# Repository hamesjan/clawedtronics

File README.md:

Claw go down
Claw go up
You get Prize

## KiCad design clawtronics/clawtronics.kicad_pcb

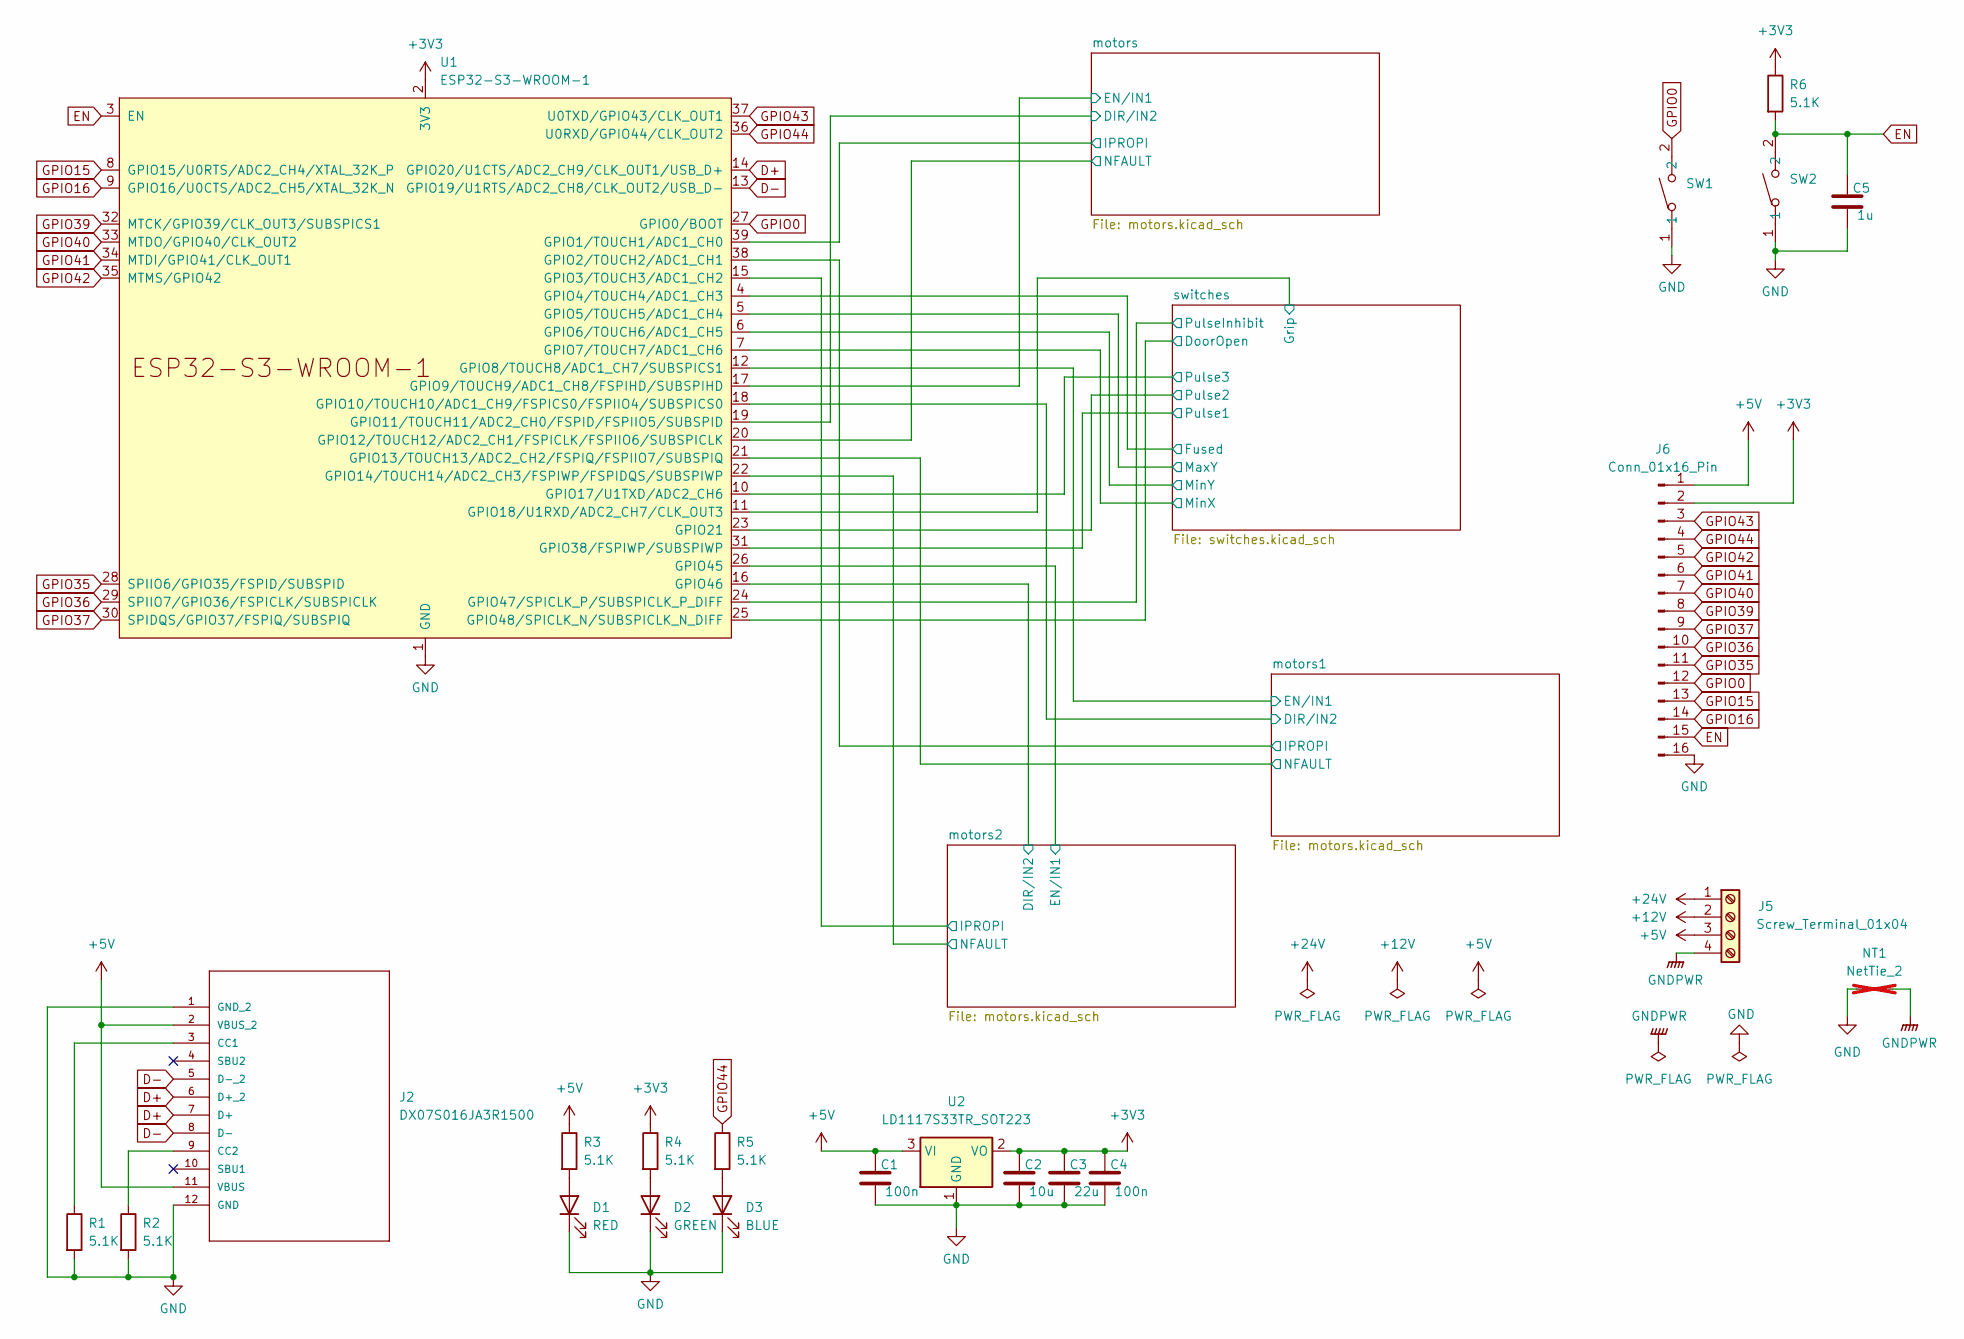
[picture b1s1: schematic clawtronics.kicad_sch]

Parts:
C1, C4: 100n; C_0603_1608Metric; Part Number C0603C104J3RACTU
C2: 10u; C_0603_1608Metric; Part Number 0603W106M6R3XD
C3: 22u; C_0603_1608Metric; Part Number 0603W226M100BD
C5: 1u; C_0603_1608Metric; Part Number 0603B105K100XD
D1: RED; LED_0603_1608Metric; Part Number SML-D12U8WT86
D2: GREEN; LED_0603_1608Metric; Part Number SML-D13M8WT86
D3: BLUE; LED_0603_1608Metric; Part Number SMLEN3BC8TT86
J2: DX07S016JA3R1500; CONN12_DX07S_JAE; MANUFACTURER_PART_NUMBER DX07S016JA3R1500
J5: Screw_Terminal_01x04; TerminalBlock_Phoenix_MKDS-1,5-4_1x04_P5.00mm_Horizontal; Part Number 1869088
J6: Conn_01x16_Pin; PinHeader_1x16_P1.00mm_Vertical; Part Number SM16B-SHLS-TF(LF)(SN)
NT1: NetTie_2; not fitted
R1, R2, R3, R4, R5, R6: 5.1K; R_0603_1608Metric; Part Number RC0603FR-105K1L
SW1, SW2: SW_SPST_TS-1088-xR020; Part Number GPTS203211B
U1: ESP32-S3-WROOM-1; Part Number ESP32-S3-WROOM-1U-N8R8
U2: LD1117S33TR_SOT223; SOT-223-3_TabPin2; Part Number LD1117S33TR

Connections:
+3V3: C2.1, C3.1, C4.1, J6.2, R4.1, R6.1, U1.2 (3V3), U2.2 (VO); also elsewhere on the board
+5V: C1.1, J2.2 (VBUS_2), J2.11 (VBUS), J5.3, J6.1, R3.1, U2.3 (VI); also elsewhere on the board
+12V: J5.2; also elsewhere on the board
+24V: J5.1; also elsewhere on the board
/motors1/DIR/IN2: U1.18 (GPIO10/TOUCH10/ADC1_CH9/FSPICS0/FSPIIO4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); also elsewhere on the board
/motors1/EN/IN1: U1.12 (GPIO8/TOUCH8/ADC1_CH7/SUBSPICS1); also elsewhere on the board
/motors1/IPROPI: U1.38 (GPIO2/TOUCH2/ADC1_CH1); also elsewhere on the board
/motors1/NFAULT: U1.21 (GPIO13/TOUCH13/ADC2_CH2/FSPIQ/FSPIIO7/S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); also elsewhere on the board
/motors2/DIR/IN2: U1.16 (GPIO46); also elsewhere on the board
/motors2/EN/IN1: U1.26 (GPIO45); also elsewhere on the board
/motors2/IPROPI: U1.15 (GPIO3/TOUCH3/ADC1_CH2); also elsewhere on the board
/motors2/NFAULT: U1.22 (GPIO14/TOUCH14/ADC2_CH3/FSPIWP/FSPIDQS/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); also elsewhere on the board
/motors/DIR/IN2: U1.19 (GPIO11/TOUCH11/ADC2_CH0/FSPID/FSPIIO5/S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); also elsewhere on the board
/motors/EN/IN1: U1.17 (GPIO9/TOUCH9/ADC1_CH8/FSPIHD/SUBSPIHD); also elsewhere on the board
/motors/IPROPI: U1.39 (GPIO1/TOUCH1/ADC1_CH0); also elsewhere on the board
/motors/NFAULT: U1.20 (GPIO12/TOUCH12/ADC2_CH1/FSPICLK/FSPIIO6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); also elsewhere on the board
/switches/DoorOpen: U1.25 (GPIO48/SPICLK_N/SUBSPICLK_N_DIFF); also elsewhere on the board
/switches/Fused: U1.4 (GPIO4/TOUCH4/ADC1_CH3); also elsewhere on the board
/switches/Grip: U1.11 (GPIO18/U1RXD/ADC2_CH7/CLK_OUT3); also elsewhere on the board
/switches/MaxY: U1.5 (GPIO5/TOUCH5/ADC1_CH4); also elsewhere on the board
/switches/MinX: U1.7 (GPIO7/TOUCH7/ADC1_CH6); also elsewhere on the board
/switches/MinY: U1.6 (GPIO6/TOUCH6/ADC1_CH5); also elsewhere on the board
/switches/Pulse1: U1.31 (GPIO38/FSPIWP/SUBSPIWP); also elsewhere on the board
/switches/Pulse2: U1.23 (GPIO21); also elsewhere on the board
/switches/Pulse3: U1.10 (GPIO17/U1TXD/ADC2_CH6); also elsewhere on the board
/switches/PulseInhibit: U1.24 (GPIO47/SPICLK_P/SUBSPICLK_P_DIFF); also elsewhere on the board
D+: J2.6 (D+_2), J2.7 (D+), U1.14 (GPIO20/U1CTS/ADC2_CH9/CLK_OUT1/USB_D+)
D-: J2.5 (D-_2), J2.8 (D-), U1.13 (GPIO19/U1RTS/ADC2_CH8/CLK_OUT2/USB_D-)
EN: C5.1, J6.15, R6.2, SW2.2, U1.3 (EN)
GND: C1.2, C2.2, C3.2, C4.2, C5.2, D1.1 (K), D2.1 (K), D3.1 (K), J2.1 (GND_2), J2.12 (GND), J6.16, NT1.1, R1.2, R2.2, SW1.1, SW2.1, U1.1 (GND), U1.40 (GND), U1.41 (GND), U2.1 (GND); also elsewhere on the board
GNDPWR: J5.4, NT1.2; also elsewhere on the board
GPIO0: J6.12, SW1.2, U1.27 (GPIO0/BOOT)
GPIO15: J6.13, U1.8 (GPIO15/U0RTS/ADC2_CH4/XTAL_32K_P)
GPIO16: J6.14, U1.9 (GPIO16/U0CTS/ADC2_CH5/XTAL_32K_N)
GPIO35: J6.11, U1.28 (SPIIO6/GPIO35/FSPID/SUBSPID)
GPIO36: J6.10, U1.29 (SPIIO7/GPIO36/FSPICLK/SUBSPICLK)
GPIO37: J6.9, U1.30 (SPIDQS/GPIO37/FSPIQ/SUBSPIQ)
GPIO39: J6.8, U1.32 (MTCK/GPIO39/CLK_OUT3/SUBSPICS1)
GPIO40: J6.7, U1.33 (MTDO/GPIO40/CLK_OUT2)
GPIO41: J6.6, U1.34 (MTDI/GPIO41/CLK_OUT1)
GPIO42: J6.5, U1.35 (MTMS/GPIO42)
GPIO43: J6.3, U1.37 (U0TXD/GPIO43/CLK_OUT1)
GPIO44: J6.4, R5.1, U1.36 (U0RXD/GPIO44/CLK_OUT2)
unnamed: D1.2 (A), R3.2
unnamed: D2.2 (A), R4.2
unnamed: D3.2 (A), R5.2
unnamed: J2.3 (CC1), R1.1
unnamed: J2.9 (CC2), R2.1

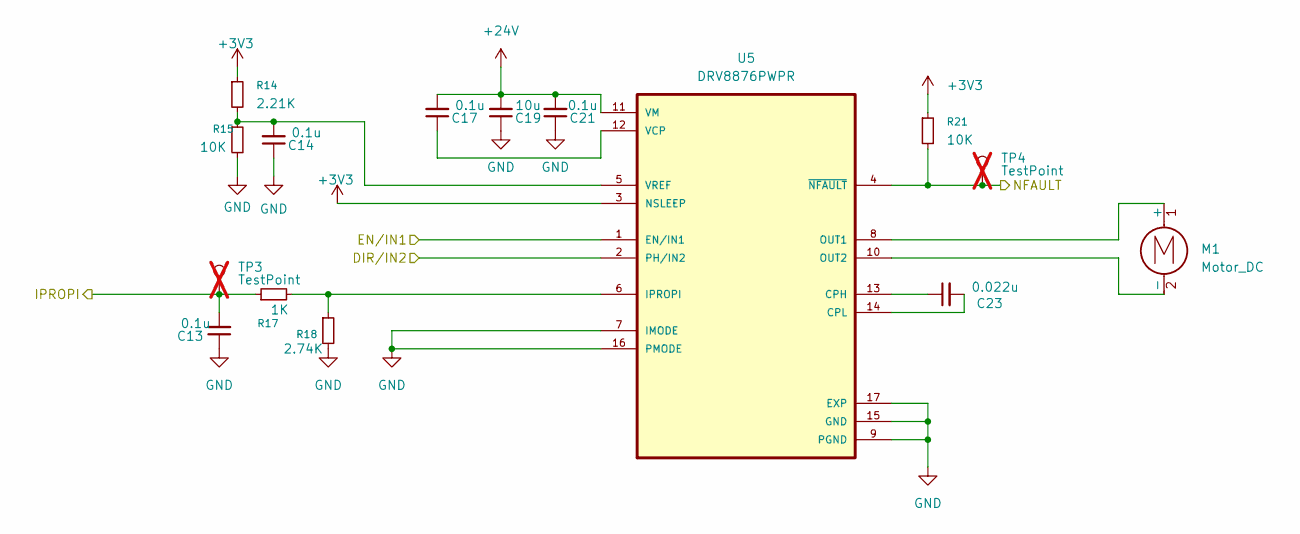
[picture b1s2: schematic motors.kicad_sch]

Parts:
C13, C14, C17, C21: 0.1u; C_0603_1608Metric; Part Number 0603B104K101XD
C19: 10u; C_0603_1608Metric; Part Number 0603W106M6R3XD
C23: 0.022u; C_0603_1608Metric; Part Number 0603B223K500SD
M1: Motor_DC; TerminalBlock_Phoenix_MKDS-1,5-2_1x02_P5.00mm_Horizontal; Part Number 1729128
R14: 2.21K; R_0603_1608Metric; Part Number RMCF0603FT2K21
R15, R21: 10K; R_0603_1608Metric; Part Number RC0603FR-0710KL
R17: 1K; R_0603_1608Metric; Part Number RMCF0603FT1K00
R18: 2.74K; R_0603_1608Metric; Part Number RMCF0603FT2K74
TP3, TP4: TestPoint; TestPoint_Pad_1.0x1.0mm; not fitted
U5: DRV8876PWPR; moto; PARTREV E

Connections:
+3V3: R14.1, R21.1, U5.3 (NSLEEP); also elsewhere on the board
+24V: C17.2, C19.2, C21.2, U5.11 (VM); also elsewhere on the board
/motors/DIR/IN2: U5.2 (PH/IN2); also elsewhere on the board
/motors/EN/IN1: U5.1 (EN/IN1); also elsewhere on the board
/motors/IPROPI: C13.2, R17.1, TP3.1 (1_1); also elsewhere on the board
/motors/NFAULT: R21.2, TP4.1 (1_1), U5.4 (~NFAULT); also elsewhere on the board
GND: C13.1, C14.1, C19.1, C21.1, R15.2, R18.2, U5.7 (IMODE), U5.9 (PGND), U5.15 (GND), U5.16 (PMODE), U5.17 (EXP); also elsewhere on the board
unnamed: M1.1 (+), U5.8 (OUT1)
unnamed: M1.2 (-), U5.10 (OUT2)
unnamed: C23.1, U5.13 (CPH)
unnamed: C23.2, U5.14 (CPL)
unnamed: R17.2, R18.1, U5.6 (IPROPI)
unnamed: C17.1, U5.12 (VCP)
unnamed: C14.2, R14.2, R15.1, U5.5 (VREF)

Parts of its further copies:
C15, C16, C18, C22, C25, C26, C27, C29: 0.1u; C_0603_1608Metric; Part Number 0603B104K101XD
C20, C28: 10u; C_0603_1608Metric; Part Number 0603W106M6R3XD
C24, C30: 0.022u; C_0603_1608Metric; Part Number 0603B223K500SD
M2, M3: Motor_DC; TerminalBlock_Phoenix_MKDS-1,5-2_1x02_P5.00mm_Horizontal; Part Number 1729128
R16, R24: 2.21K; R_0603_1608Metric; Part Number RMCF0603FT2K21
R19, R23, R25, R30: 10K; R_0603_1608Metric; Part Number RC0603FR-0710KL
R20, R26: 1K; R_0603_1608Metric; Part Number RMCF0603FT1K00
R22, R27: 2.74K; R_0603_1608Metric; Part Number RMCF0603FT2K74
TP5, TP6, TP7, TP9: TestPoint; TestPoint_Pad_1.0x1.0mm; not fitted
U7, U8: DRV8876PWPR; moto; PARTREV E

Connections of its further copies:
+3V3: R16.1, R23.1, R24.1, R30.1, U7.3 (NSLEEP), U8.3 (NSLEEP); also elsewhere on the board
+24V: C18.2, C20.2, C22.2, C27.2, C28.2, C29.2, U7.11 (VM), U8.11 (VM); also elsewhere on the board
/motors1/DIR/IN2: U7.2 (PH/IN2); also elsewhere on the board
/motors1/EN/IN1: U7.1 (EN/IN1); also elsewhere on the board
/motors1/IPROPI: C15.2, R20.1, TP5.1 (1_1); also elsewhere on the board
/motors1/NFAULT: R23.2, TP6.1 (1_1), U7.4 (~NFAULT); also elsewhere on the board
/motors2/DIR/IN2: U8.2 (PH/IN2); also elsewhere on the board
/motors2/EN/IN1: U8.1 (EN/IN1); also elsewhere on the board
/motors2/IPROPI: C25.2, R26.1, TP7.1 (1_1); also elsewhere on the board
/motors2/NFAULT: R30.2, TP9.1 (1_1), U8.4 (~NFAULT); also elsewhere on the board
GND: C15.1, C16.1, C20.1, C22.1, C25.1, C26.1, C28.1, C29.1, R19.2, R22.2, R25.2, R27.2, U7.7 (IMODE), U7.9 (PGND), U7.15 (GND), U7.16 (PMODE), U7.17 (EXP), U8.7 (IMODE), U8.9 (PGND), U8.15 (GND), U8.16 (PMODE), U8.17 (EXP); also elsewhere on the board
unnamed: M2.1 (+), U7.8 (OUT1)
unnamed: M2.2 (-), U7.10 (OUT2)
unnamed: M3.1 (+), U8.8 (OUT1)
unnamed: M3.2 (-), U8.10 (OUT2)
unnamed: C24.1, U7.13 (CPH)
unnamed: C24.2, U7.14 (CPL)
unnamed: R20.2, R22.1, U7.6 (IPROPI)
unnamed: C18.1, U7.12 (VCP)
unnamed: C16.2, R16.2, R19.1, U7.5 (VREF)
unnamed: C30.1, U8.13 (CPH)
unnamed: C30.2, U8.14 (CPL)
unnamed: R26.2, R27.1, U8.6 (IPROPI)
unnamed: C27.1, U8.12 (VCP)
unnamed: C26.2, R24.2, R25.1, U8.5 (VREF)

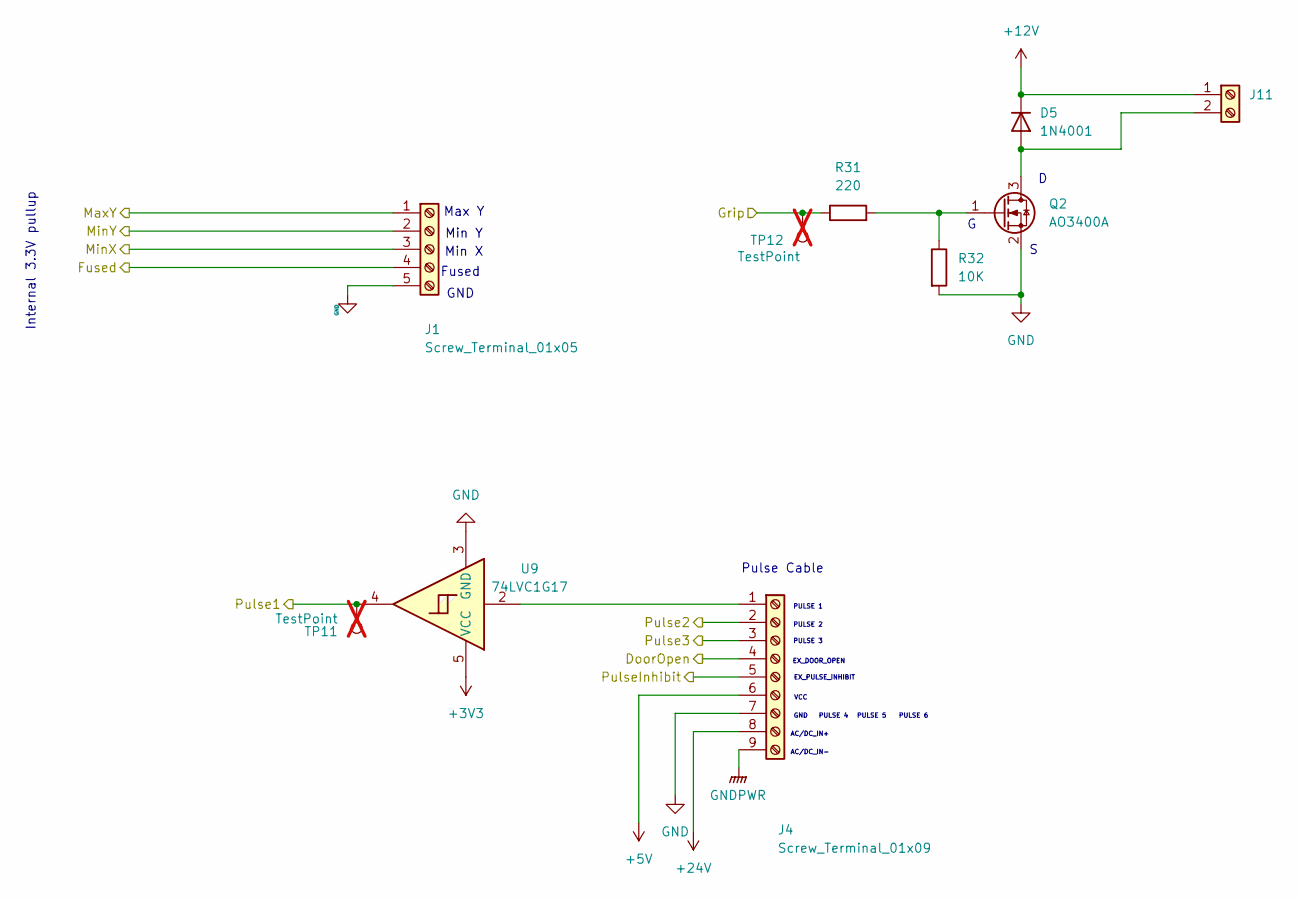
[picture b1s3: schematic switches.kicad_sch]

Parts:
D5: 1N4001; D_DO-41_SOD81_P10.16mm_Horizontal; Part Number 1N4001
J1: Screw_Terminal_01x05; TerminalBlock_Phoenix_MKDS-1,5-5_1x05_P5.00mm_Horizontal; Part Number 1869091
J4: Screw_Terminal_01x09; TerminalBlock_Phoenix_MKDS-1,5-9_1x09_P5.00mm_Horizontal; Part Number Put 5 + 4 together
J11: Screw_Terminal_01x02; TerminalBlock_Phoenix_MKDS-1,5-2_1x02_P5.00mm_Horizontal; Part Number 1729128
Q2: AO3400A; SOT-23; Part Number AO3400A
R31: 220; R_0603_1608Metric; Part Number RMCF0603JT220R
R32: 10K; R_0603_1608Metric; Part Number RC0603FR-0710KL
TP11, TP12: TestPoint; TestPoint_Pad_1.0x1.0mm; not fitted
U9: 74LVC1G17; Texas_X2SON-5_0.8x0.8mm_P0.48mm_RoutingVia; Part Number 74LVC1G17

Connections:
+3V3: U9.5 (VCC); also elsewhere on the board
+5V: J4.6; also elsewhere on the board
+12V: D5.1 (K), J11.1; also elsewhere on the board
+24V: J4.8; also elsewhere on the board
/switches/DoorOpen: J4.4; also elsewhere on the board
/switches/Fused: J1.4; also elsewhere on the board
/switches/Grip: R31.1, TP12.1 (1_1); also elsewhere on the board
/switches/MaxY: J1.1; also elsewhere on the board
/switches/MinX: J1.3; also elsewhere on the board
/switches/MinY: J1.2; also elsewhere on the board
/switches/Pulse1: TP11.1 (1_1), U9.4; also elsewhere on the board
/switches/Pulse2: J4.2; also elsewhere on the board
/switches/Pulse3: J4.3; also elsewhere on the board
/switches/PulseInhibit: J4.5; also elsewhere on the board
GND: J1.5, J4.7, Q2.2 (S), R32.2, U9.3 (GND); also elsewhere on the board
GNDPWR: J4.9; also elsewhere on the board
unnamed: D5.2 (A), J11.2, Q2.3 (D)
unnamed: J4.1, U9.2
unnamed: Q2.1 (G), R31.2, R32.1

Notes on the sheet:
EX_PULSE_INHIBIT
PULSE 1
GND
VCC
Min Y
PULSE 5
Internal 3.3V pullup
PULSE 4
EX_DOOR_OPEN
PULSE 2
PULSE 6
AC/DC_IN-
Fused
Max Y
AC/DC_IN+
Min X
Pulse Cable
PULSE 3

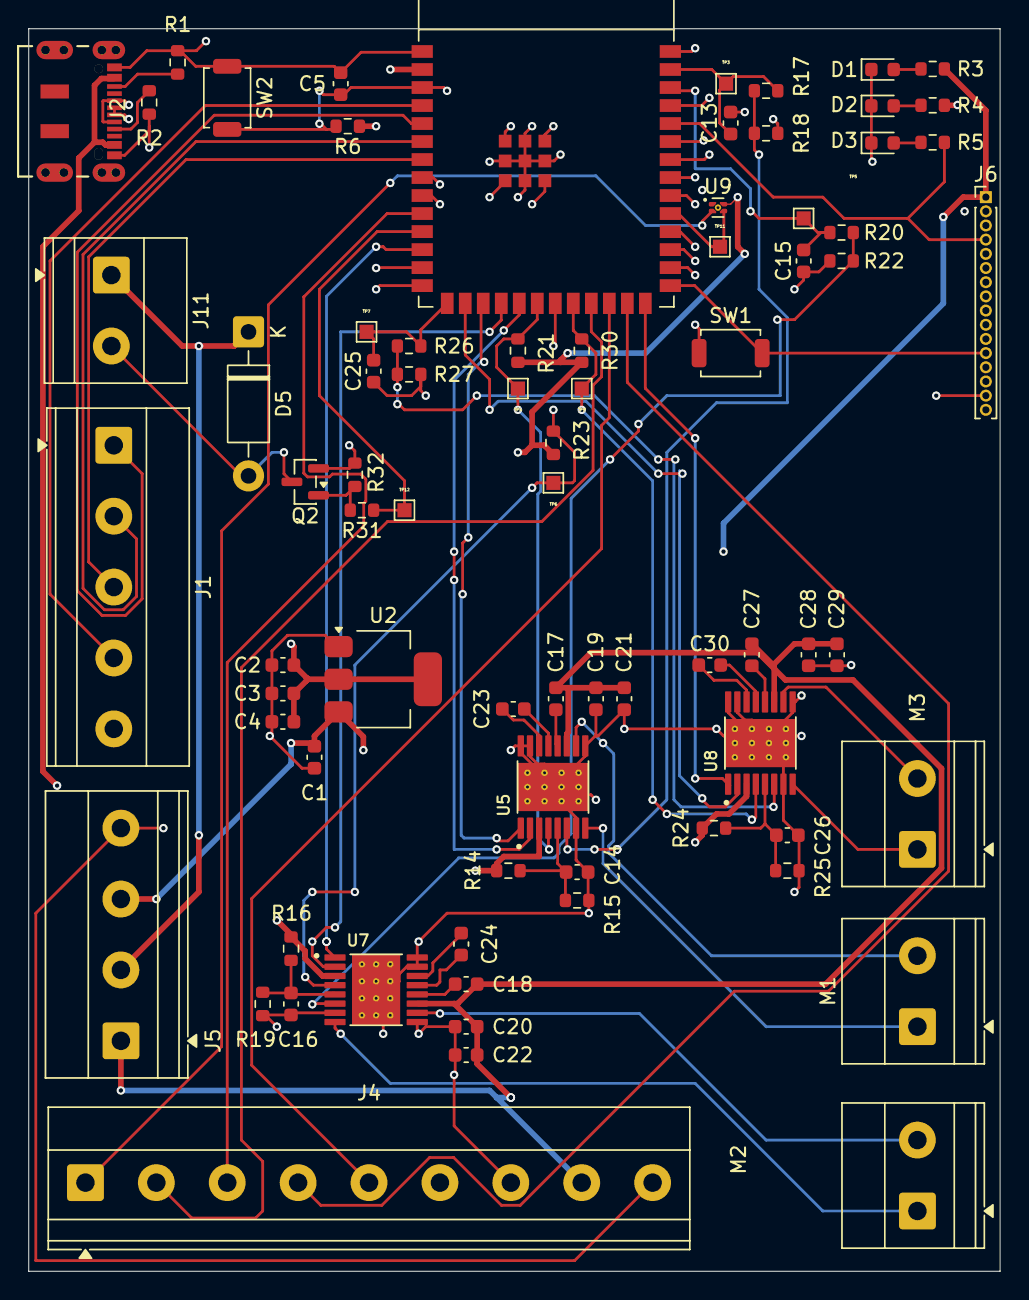
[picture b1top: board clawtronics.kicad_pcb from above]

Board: 4 copper layers, 68.5 x 87.6 mm, 76 parts (0 on the bottom side), 72 nets.

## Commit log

2026-03-04 init the journey
2026-03-15 adding esp app
2026-03-15 name
2026-03-15 testing ssh
2026-03-15 tokenizin
2026-03-19 adding mdb esp32
2026-04-03 update pcbs with otors
2026-04-12 pcb progress
2026-04-14 add pcb
2026-04-23 figured out switches
2026-04-30 layout with hierarchical sheets
2026-04-30 layout so far
2026-04-30 finished layout
2026-04-30 made geber files
2026-05-04 update BOM with PNs
2026-05-14 add parts list and order sheet
2026-05-31 v1 assembly and experiment
2026-05-31 Add game instructions to README
2026-06-06 moving on to v2
2026-06-06 update footprints

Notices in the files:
parts and their libraries:
COPYRIGHT: Copyright (C) 2025 Ultra Librarian. All rights reserved.
